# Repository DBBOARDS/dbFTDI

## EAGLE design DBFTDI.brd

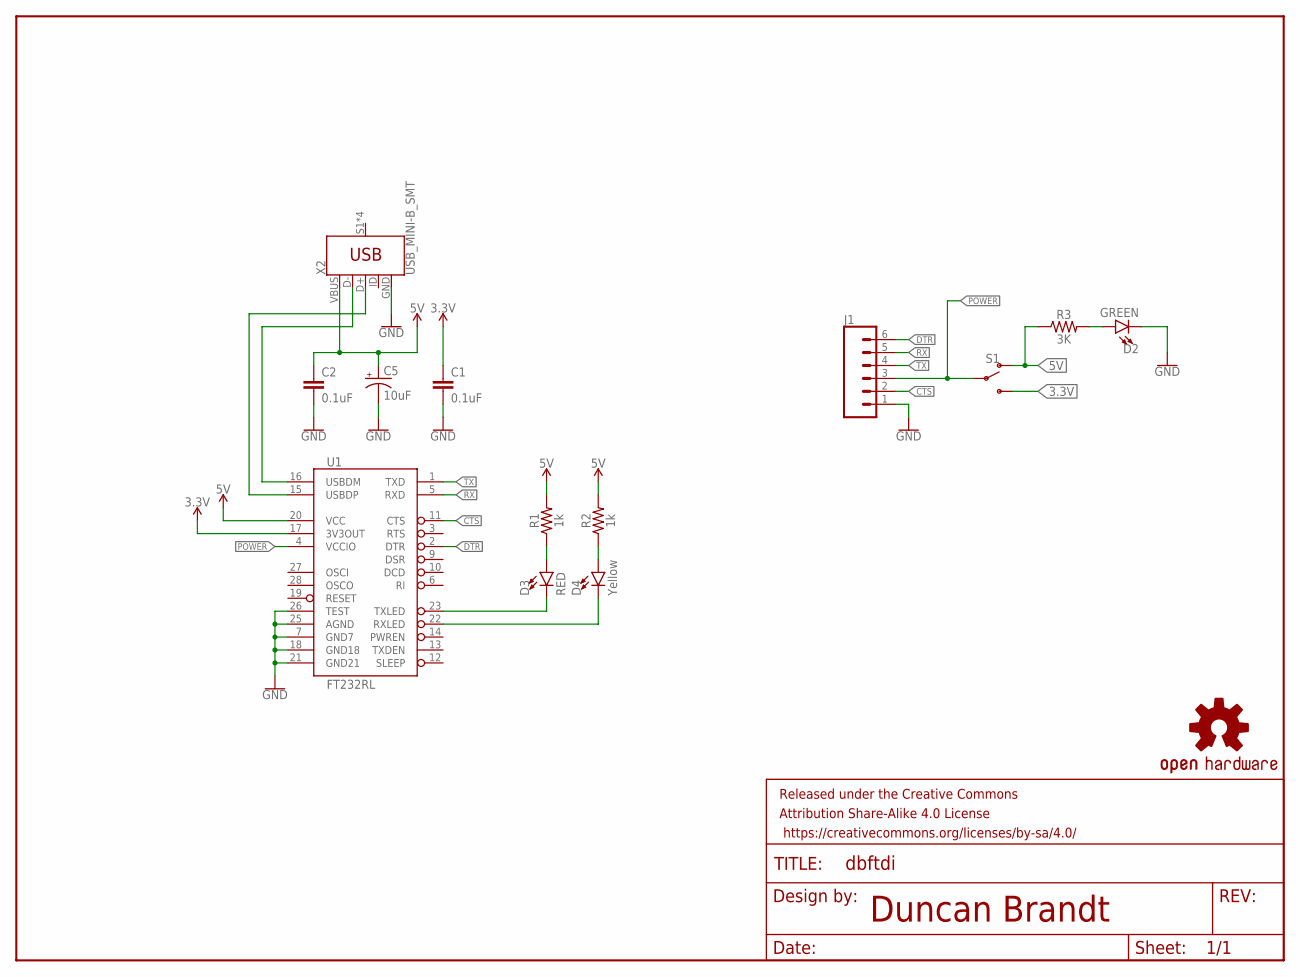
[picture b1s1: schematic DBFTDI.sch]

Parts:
C1, C2: 0.1uF; 0603
C5: 10uF; EIA3216
D2: GREEN; LED-1206
D3: RED; LED-1206
D4: Yellow; LED-1206
FRAME1: FRAME-LETTER; CREATIVE_COMMONS
J1: CONN_06SILK_FEMALE_PTH; 1X06
LOGO1: OSHW-LOGOL; OSHW-LOGO-L
R1, R2: 1k; 0603
R3: 3K; 0603
S1: SWITCH-SPDT-SMD-AYZ0202; SWITCH_DPDT_SMD_AYZ0202
U1: FT232RL; SSOP28DB
X2: USB_MINI-B_SMT; USB-MINIB

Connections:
3.3V: C1.1, S1.3 (S), U1.17 (3V3OUT)
5V: C2.1, C5.+, R1.2, R2.2, R3.1, S1.1 (O), U1.20 (VCC), X2.VBUS
CTS: J1.2, U1.11 (CTS)
DTR: J1.6, U1.2 (DTR)
GND: C1.2, C2.2, C5.-, D2.C, J1.1, U1.7 (GND7), U1.18 (GND18), U1.21 (GND21), U1.25 (AGND), U1.26 (TEST), X2.GND
unnamed: D3.A, R1.1
unnamed: D4.A, R2.1
unnamed: D2.A, R3.2
unnamed: U1.15 (USBDP), X2.D+
unnamed: U1.16 (USBDM), X2.D-
POWER: J1.3, S1.2, U1.4 (VCCIO)
RX: J1.5, U1.5 (RXD)
RXLED: D4.C, U1.22 (RXLED)
TX: J1.4, U1.1 (TXD)
TXLED: D3.C, U1.23 (TXLED)

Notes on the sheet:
Duncan Brandt

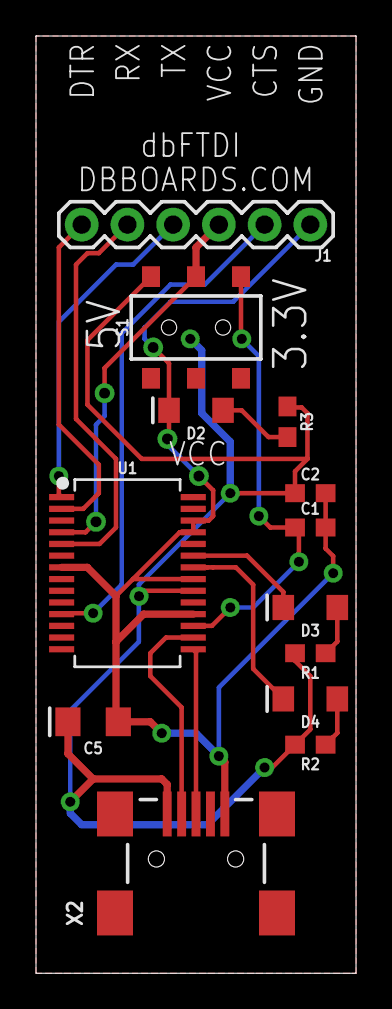
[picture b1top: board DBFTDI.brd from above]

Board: 2 copper layers, 17.8 x 52.1 mm, 15 parts (1 on the bottom side), 15 nets.

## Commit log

2019-01-24 DBFTDI Eagle Files
    schematic and board files

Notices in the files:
parts and their libraries:
DB-LED: Licensing: Creative Commons ShareAlike 4.0 International - https://creativecommons.org/licenses/by-sa/4.0
DB-SYMBOLS: Released under the Creative Commons Attribution Share-Alike 4.0 License
DB-SYMBOLS: https://creativecommons.org/licenses/by-sa/4.0
